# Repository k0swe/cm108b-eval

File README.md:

Evaluation board for the CMedia CM108B USB audio controller.

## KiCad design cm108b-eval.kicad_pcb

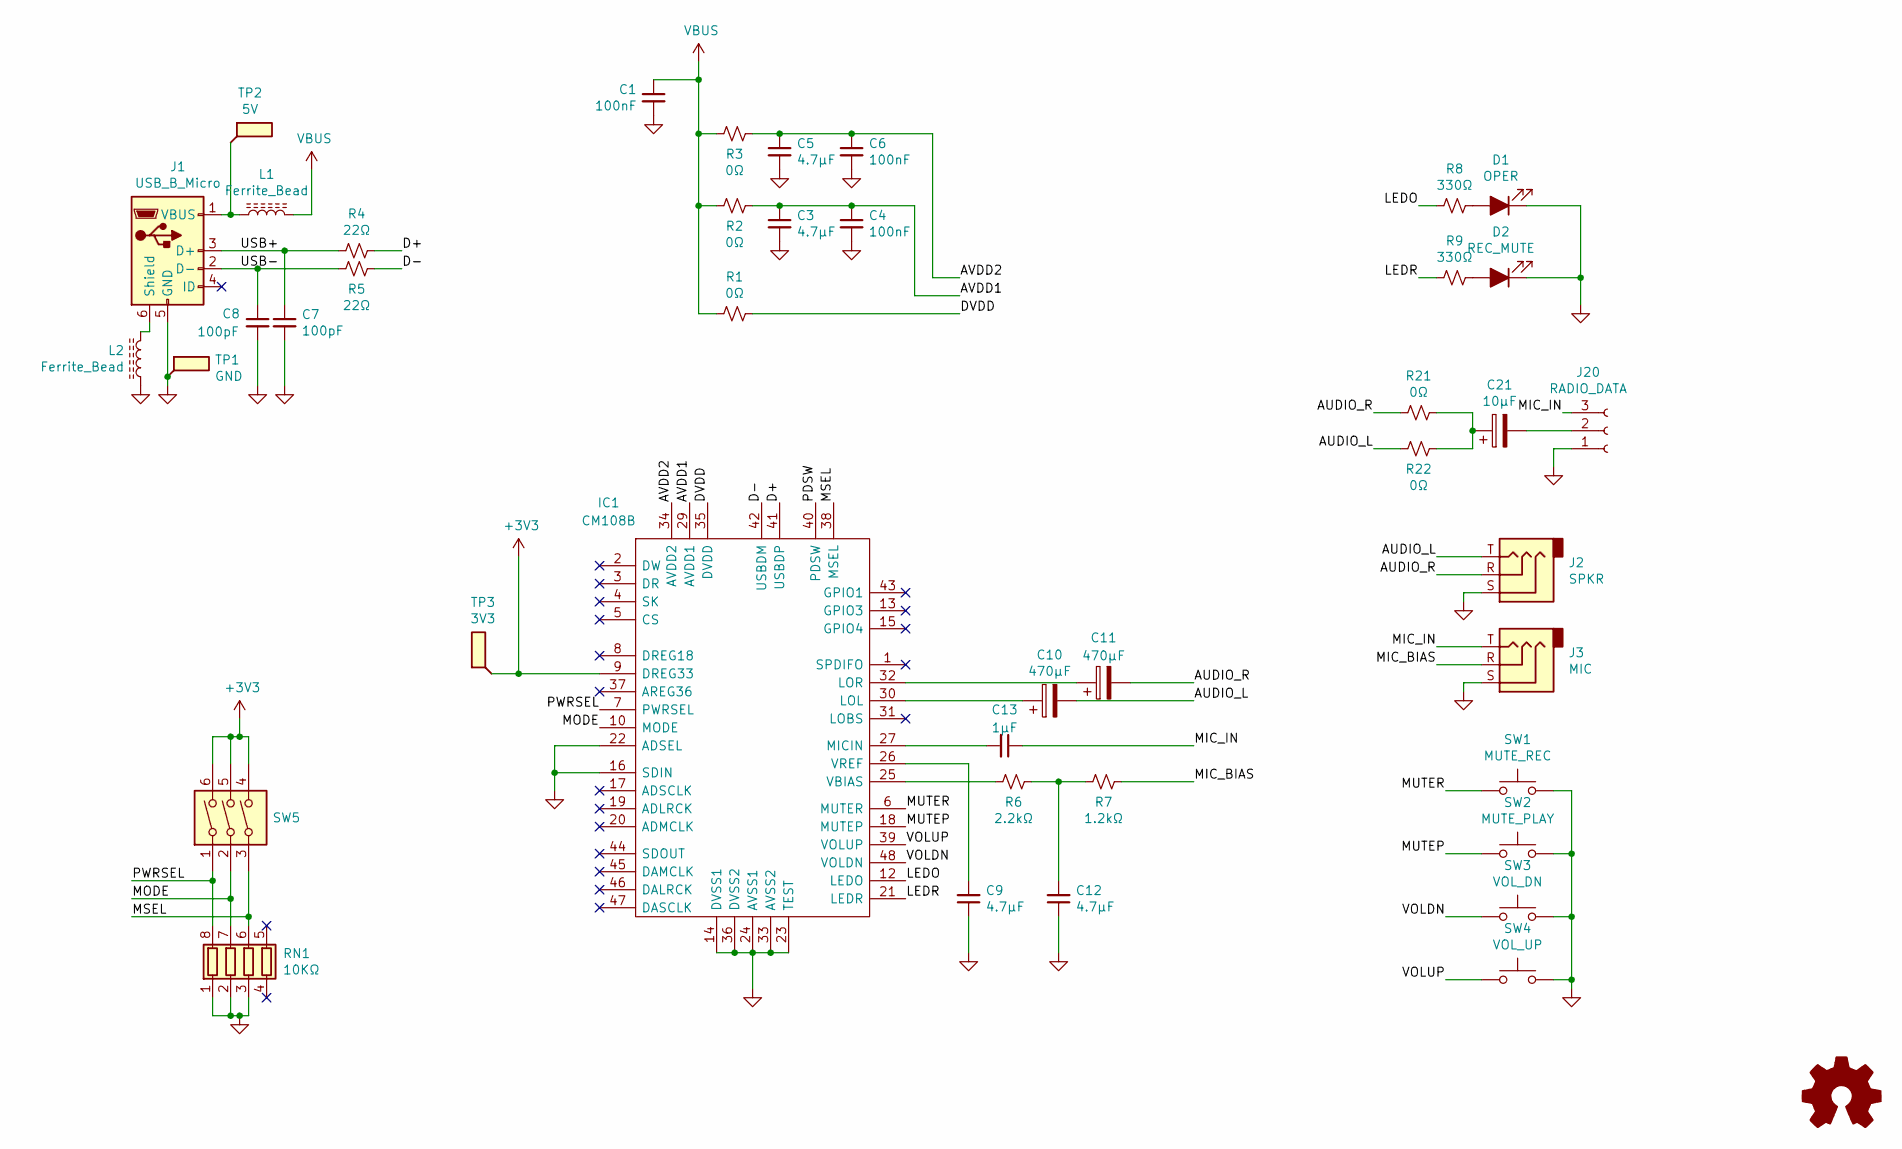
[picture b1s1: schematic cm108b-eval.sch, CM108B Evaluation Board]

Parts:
C1, C4, C6: 100nF; C_1210_3225Metric
C3, C5, C9, C12: 4.7μF; C_1210_3225Metric
C7, C8: 100pF; C_1210_3225Metric
C10, C11: 470μF; CAPPM7343X430N
C13: 1μF; C_1210_3225Metric
C21: 10μF; C_1210_3225Metric
D1: OPER; LED_0603_1608Metric
D2: REC_MUTE; LED_0603_1608Metric
IC1: CM108B; LQFP-48_7x7mm_P0.5mm
J1: USB_B_Micro; UJ2-MIBH-4-SMT
J2: SPKR; Jack_3.5mm_CUI_SJ-3524-SMT_Horizontal
J3: MIC; Jack_3.5mm_CUI_SJ-3524-SMT_Horizontal
J20: RADIO_DATA; JST_PH_B3B-PH-SM4-TB_1x03-1MP_P2.00mm_Vertical
L1, L2: Ferrite_Bead; L_1210_3225Metric
LOGO1: Logo_Open_Hardware_Small; OSHW-Logo2_9.8x8mm_SilkScreen
R1, R2, R3, R21, R22: 0Ω; R_1210_3225Metric
R4, R5: 22Ω; R_1210_3225Metric
R6: 2.2kΩ; R_1210_3225Metric
R7: 1.2kΩ; R_1210_3225Metric
R8, R9: 330Ω; R_1210_3225Metric
RN1: 10KΩ; R_Array_Concave_4x0402
SW1: MUTE_REC; SW_SPST_Omron_B3FS-100xP
SW2: MUTE_PLAY; SW_SPST_Omron_B3FS-100xP
SW3: VOL_DN; SW_SPST_Omron_B3FS-100xP
SW4: VOL_UP; SW_SPST_Omron_B3FS-100xP
SW5: SW_DIP_x03; 416131160803
TP1: GND; TestPoint_Pad_D2.0mm
TP2: 5V; TestPoint_Pad_D1.0mm
TP3: 3V3; TestPoint_Pad_D1.0mm

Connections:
+3V3: IC1.9 (DREG33), SW5.4, SW5.5, SW5.6, TP3.1
/AUDIO_L: C10.2, J2.T, R22.2
/AUDIO_R: C11.2, J2.R, R21.2
/AVDD1: C3.1, C4.1, IC1.29 (AVDD1), R2.1
/AVDD2: C5.1, C6.1, IC1.34 (AVDD2), R3.1
/D+: IC1.41 (USBDP), R4.1
/D-: IC1.42 (USBDM), R5.1
/DVDD: IC1.35 (DVDD), R1.1
/LEDO: IC1.12 (LEDO), R8.2
/LEDR: IC1.21 (LEDR), R9.2
/MIC_BIAS: J3.R, R7.1
/MIC_IN: C13.1, J3.T, J20.3
/MODE: IC1.10 (MODE), RN1.7 (R2.2), SW5.2
/MSEL: IC1.38 (MSEL), RN1.6 (R3.2), SW5.3
/MUTEP: IC1.18 (MUTEP), SW2.1
/MUTER: IC1.6 (MUTER), SW1.1
/PWRSEL: IC1.7 (PWRSEL), RN1.8 (R1.2), SW5.1
/USB+: C7.1, J1.3 (D+), R4.2
/USB-: C8.1, J1.2 (D-), R5.2
/VOLDN: IC1.48 (VOLDN), SW3.1
/VOLUP: IC1.39 (VOLUP), SW4.1
GND: C1.2, C3.2, C4.2, C5.2, C6.2, C7.2, C8.2, C9.1, C12.1, D1.1 (K), D2.1 (K), IC1.14 (DVSS1), IC1.16 (SDIN), IC1.22 (ADSEL), IC1.23 (TEST), IC1.24 (AVSS1), IC1.33 (AVSS2), IC1.36 (DVSS2), J1.5 (GND), J2.S, J3.S, J20.1, L2.1, RN1.1 (R1.1), RN1.2 (R2.1), RN1.3 (R3.1), SW1.2, SW2.2, SW3.2, SW4.2, TP1.1
unnamed: C9.2, IC1.26 (VREF)
unnamed: C10.1, IC1.30 (LOL)
unnamed: C11.1, IC1.32 (LOR)
unnamed: C12.2, R6.1, R7.2
unnamed: C13.2, IC1.27 (MICIN)
unnamed: C21.1, R21.1, R22.1
unnamed: C21.2, J20.2
unnamed: D1.2 (A), R8.1
unnamed: D2.2 (A), R9.1
unnamed: IC1.25 (VBIAS), R6.2
unnamed: J1.1 (VBUS), L1.1, TP2.1
unnamed: J1.6 (Shield), L2.2
VBUS: C1.1, L1.2, R1.2, R2.2, R3.2

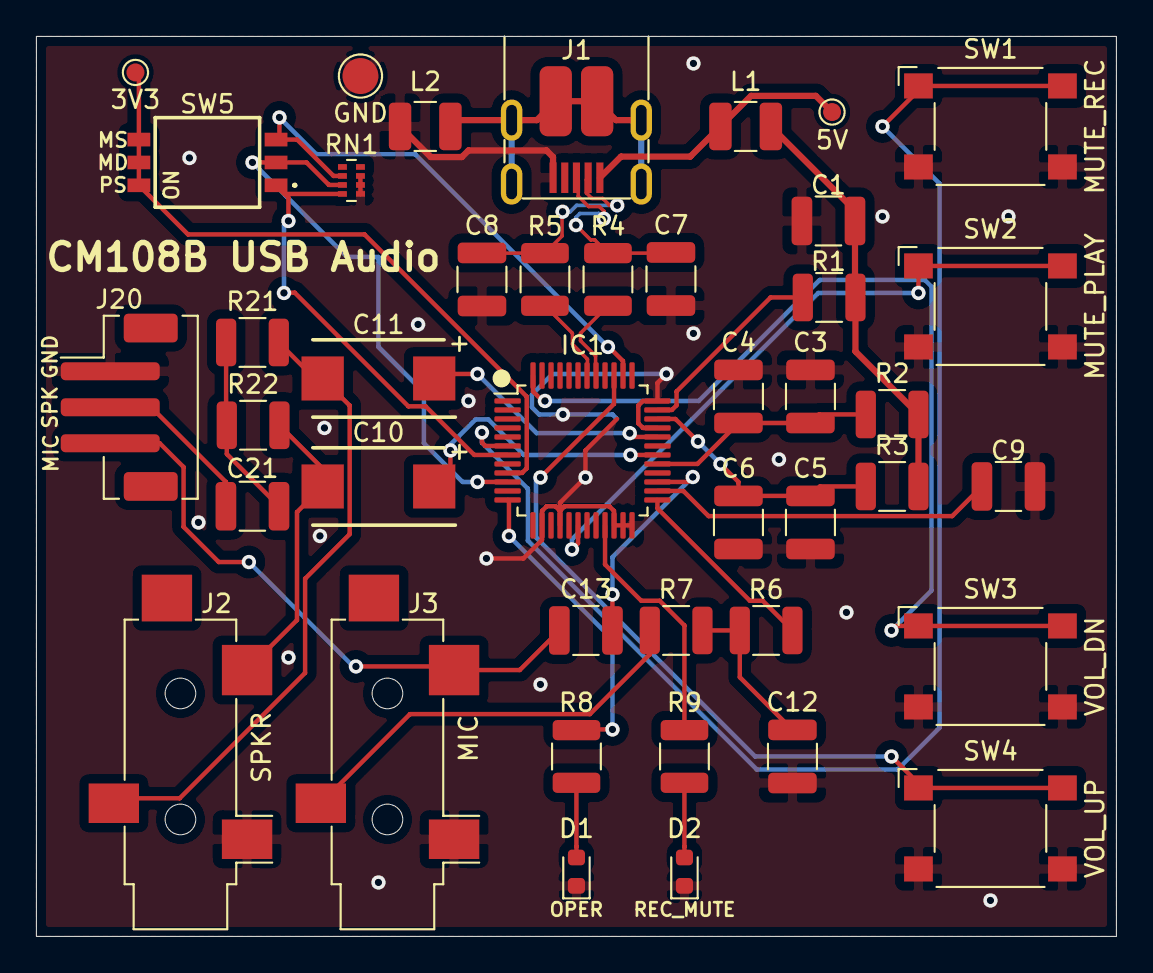
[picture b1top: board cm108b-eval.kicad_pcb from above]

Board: 2 copper layers, 60.0 x 50.0 mm, 43 parts (1 on the bottom side), 35 nets.

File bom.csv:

Refs,value,Vendor,Vendor Part #,Price,datasheet,footprint
C1,100nF,Mouser,80-C1210C104K5RAUTO,0.37,https://www.mouser.com/datasheet/2/212/KEM_C1023_X7R_AUTO_SM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,Capacitor_SMD:C_1210_3225Metric
C10,470μF,Mouser,74-293D477X9010E2TE3,1.3,https://www.mouser.com/datasheet/2/427/293d-1763499.pdf,Vishay:CAPPM7343X430N
C11,470μF,Mouser,74-293D477X9010E2TE3,1.3,https://www.mouser.com/datasheet/2/427/293d-1763499.pdf,Vishay:CAPPM7343X430N
C12,4.7μF,Mouser,963-EMK325B7475MN-T,0.35,https://www.mouser.com/datasheet/2/396/mlcc02_e-1307760.pdf,Capacitor_SMD:C_1210_3225Metric
C13,1μF,Mouser,791-1210B105M101CT,0.13,https://www.mouser.com/datasheet/2/210/WTC_MLCC_General_Purp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,Capacitor_SMD:C_1210_3225Metric
C21,10μF,Mouser,791-1210F106Z100CT,0.29,https://www.mouser.com/datasheet/2/210/WTC_MLCC_General_Purp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,Capacitor_SMD:C_1210_3225Metric
C3,4.7μF,Mouser,963-EMK325B7475MN-T,0.35,https://www.mouser.com/datasheet/2/396/mlcc02_e-1307760.pdf,Capacitor_SMD:C_1210_3225Metric
C4,100nF,Mouser,80-C1210C104K5RAUTO,0.37,https://www.mouser.com/datasheet/2/212/KEM_C1023_X7R_AUTO_SM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,Capacitor_SMD:C_1210_3225Metric
C5,4.7μF,Mouser,963-EMK325B7475MN-T,0.35,https://www.mouser.com/datasheet/2/396/mlcc02_e-1307760.pdf,Capacitor_SMD:C_1210_3225Metric
C6,100nF,Mouser,80-C1210C104K5RAUTO,0.37,https://www.mouser.com/datasheet/2/212/KEM_C1023_X7R_AUTO_SM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,Capacitor_SMD:C_1210_3225Metric
C7,100pF,Mouser,80-C1210C101K3HACTU,0.28,https://www.mouser.com/datasheet/2/212/KEM_C1007_X8R_ULTRA_1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,Capacitor_SMD:C_1210_3225Metric
C8,100pF,Mouser,80-C1210C101K3HACTU,0.28,https://www.mouser.com/datasheet/2/212/KEM_C1007_X8R_ULTRA_1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,Capacitor_SMD:C_1210_3225Metric
C9,4.7μF,Mouser,963-EMK325B7475MN-T,0.35,https://www.mouser.com/datasheet/2/396/mlcc02_e-1307760.pdf,Capacitor_SMD:C_1210_3225Metric
D1,OPER,Mouser,710-150060RS75000,0.15,https://www.mouser.com/datasheet/2/445/150060RS75000-1715052.pdf,LED_SMD:LED_0603_1608Metric
D2,REC_MUTE,Mouser,710-150060RS75000,0.15,https://www.mouser.com/datasheet/2/445/150060RS75000-1715052.pdf,LED_SMD:LED_0603_1608Metric
IC1,CM108B,Symmetry,CM108B,1.64,https://www.cmedia.com.tw/support/download_center/38,Package_QFP:LQFP-48_7x7mm_P0.5mm
J1,USB_B_Micro,Mouser,490-UJ2-MIBH-4-SMT,0.79,https://www.mouser.com/datasheet/2/670/uj2_mibh_4_smt-1313358.pdf,CUI:UJ2-MIBH-4-SMT
J2,SPKR,Mouser,490-SJ3524-SMT-TR-GR,1.26,https://www.mouser.com/datasheet/2/670/sj_352x_smt-1779397.pdf,Connector_Audio:Jack_3.5mm_CUI_SJ-3524-SMT_Horizontal
J20,RADIO_DATA,Mouser,485-4389,0.35,https://www.mouser.com/datasheet/2/737/4389_C13924-001_CCP-W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,Connector_JST:JST_PH_B3B-PH-SM4-TB_1x03-1MP_P2.00mm_Vertical
J3,MIC,Mouser,490-SJ3524SMTTRPI,1.26,https://www.mouser.com/datasheet/2/670/sj_352x_smt-1779397.pdf,Connector_Audio:Jack_3.5mm_CUI_SJ-3524-SMT_Horizontal
L1,Ferrite_Bead,Mouser,673-PE1210CCMC161STS,0.92,https://www.mouser.com/datasheet/2/336/W719-1480588.pdf,Inductor_SMD:L_1210_3225Metric
L2,Ferrite_Bead,Mouser,673-PE1210CCMC161STS,0.92,https://www.mouser.com/datasheet/2/336/W719-1480588.pdf,Inductor_SMD:L_1210_3225Metric
R1,0Ω,Mouser,660-RK73Z2ETTD,0.14,https://www.mouser.com/datasheet/2/219/RK73Z-1825387.pdf,Resistor_SMD:R_1210_3225Metric
R2,0Ω,Mouser,660-RK73Z2ETTD,0.14,https://www.mouser.com/datasheet/2/219/RK73Z-1825387.pdf,Resistor_SMD:R_1210_3225Metric
R21,0Ω,Mouser,660-RK73Z2ETTD,0.14,https://www.mouser.com/datasheet/2/219/RK73Z-1825387.pdf,Resistor_SMD:R_1210_3225Metric
R22,0Ω,Mouser,660-RK73Z2ETTD,0.14,https://www.mouser.com/datasheet/2/219/RK73Z-1825387.pdf,Resistor_SMD:R_1210_3225Metric
R3,0Ω,Mouser,660-RK73Z2ETTD,0.14,https://www.mouser.com/datasheet/2/219/RK73Z-1825387.pdf,Resistor_SMD:R_1210_3225Metric
R4,22Ω,Mouser,667-ERJ-14YJ220U,0.17,https://www.mouser.com/datasheet/2/315/AOA0000C301-1488782.pdf,Resistor_SMD:R_1210_3225Metric
R5,22Ω,Mouser,667-ERJ-14YJ220U,0.17,https://www.mouser.com/datasheet/2/315/AOA0000C301-1488782.pdf,Resistor_SMD:R_1210_3225Metric
R6,2.2kΩ,Mouser,660-RK73H2ETTD2201F,0.2,https://www.mouser.com/datasheet/2/219/RK73H-1825326.pdf,Resistor_SMD:R_1210_3225Metric
R7,1.2kΩ,Mouser,603-RC1210FR-071K2L,0.16,https://www.mouser.com/datasheet/2/447/PYu_RC_Group_51_RoHS_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,Resistor_SMD:R_1210_3225Metric
R8,330Ω,Mouser,279-CRGCQ1210J330R,0.13,https://www.mouser.com/datasheet/2/418/4/NG_DS_1773204-3_1-1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,Resistor_SMD:R_1210_3225Metric
R9,330Ω,Mouser,279-CRGCQ1210J330R,0.13,https://www.mouser.com/datasheet/2/418/4/NG_DS_1773204-3_1-1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,Resistor_SMD:R_1210_3225Metric
RN1,10KΩ,Mouser,652-CAT10A-103J2LF,0.1,https://www.mouser.com/datasheet/2/54/CAT10-1954944.pdf,Resistor_SMD:R_Array_Concave_4x0402
SW1,MUTE_REC,Mouser,653-B3FS-1002P,0.58,https://www.mouser.com/datasheet/2/307/omron_B3FS-1189765.pdf,Omron:SW_SPST_Omron_B3FS-100xP
SW2,MUTE_PLAY,Mouser,653-B3FS-1002P,0.58,https://www.mouser.com/datasheet/2/307/omron_B3FS-1189765.pdf,Omron:SW_SPST_Omron_B3FS-100xP
SW3,VOL_DN,Mouser,653-B3FS-1002P,0.58,https://www.mouser.com/datasheet/2/307/omron_B3FS-1189765.pdf,Omron:SW_SPST_Omron_B3FS-100xP
SW4,VOL_UP,Mouser,653-B3FS-1002P,0.58,https://www.mouser.com/datasheet/2/307/omron_B3FS-1189765.pdf,Omron:SW_SPST_Omron_B3FS-100xP
SW5,SW_DIP_x03,Mouser,710-416131160803,3.31,https://www.mouser.com/datasheet/2/445/416131160803-1717247.pdf,Wurth:416131160803

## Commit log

2021-03-22 Initial commit, WIP
2021-03-22 Schematic finished
    Mostly based on CM108 application note, with changes for CM108B differences. No crystal, no REGV, and I don't know what the LED in J1 is supposed to be.
2021-03-22 Add schematic
2021-03-22 Footprints assigned
2021-03-23 Change capacitors from exponential notation to units
2021-03-23 PCB laid out
2021-03-23 Completed BOM
2021-03-23 Move inductor to USB cable shield
    Having it on the cable's ground pin just doesn't make sense to me.
2021-04-03 Add some 3D models
2021-04-04 Convert BOM from one per line to grouped
2021-04-05 Thicker power traces
2021-04-07 Fix USB connector from A to micro-B
2021-04-07 Couple of silkscreen improvements
2021-04-10 Retool for JLCPCB assembly
2021-04-10 Update BOM
2021-04-10 Remove unnecessary fields from schema
2021-04-10 Swap Shou_Han USB socket for BoomElec
    I wanted to see if JLCPCB SMT Assembly could support BoomElec, but it doesn't.
2021-04-14 Update micro USB part, and clean up libraries
    The Molex micro USB is nearly impossible to hand solder, so I'm moving to the CUI
2021-04-15 Add CC-BY-4.0 license
2021-04-15 Add CUI USB 3D model
2021-04-15 Add CUI phone jack 3D models
2021-04-15 Add more test points
2021-04-15 Move 5V test point to directly off USB
2021-04-18 Incorporate learnings from first physical prototype
    * Button footprint pad numberings are wrong for symbol, so they were always pressed
    * Turn J3 for solderability
2021-04-19 Fix up BOM
2021-04-21 Fix R and L on J1
    Resolves #1
2021-04-21 Copy from HS100B project to get identical layouts
2021-04-24 Add OSHW logo

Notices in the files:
cm108b-eval.sch:
Licensed under Creative Commons CC-BY-4.0
